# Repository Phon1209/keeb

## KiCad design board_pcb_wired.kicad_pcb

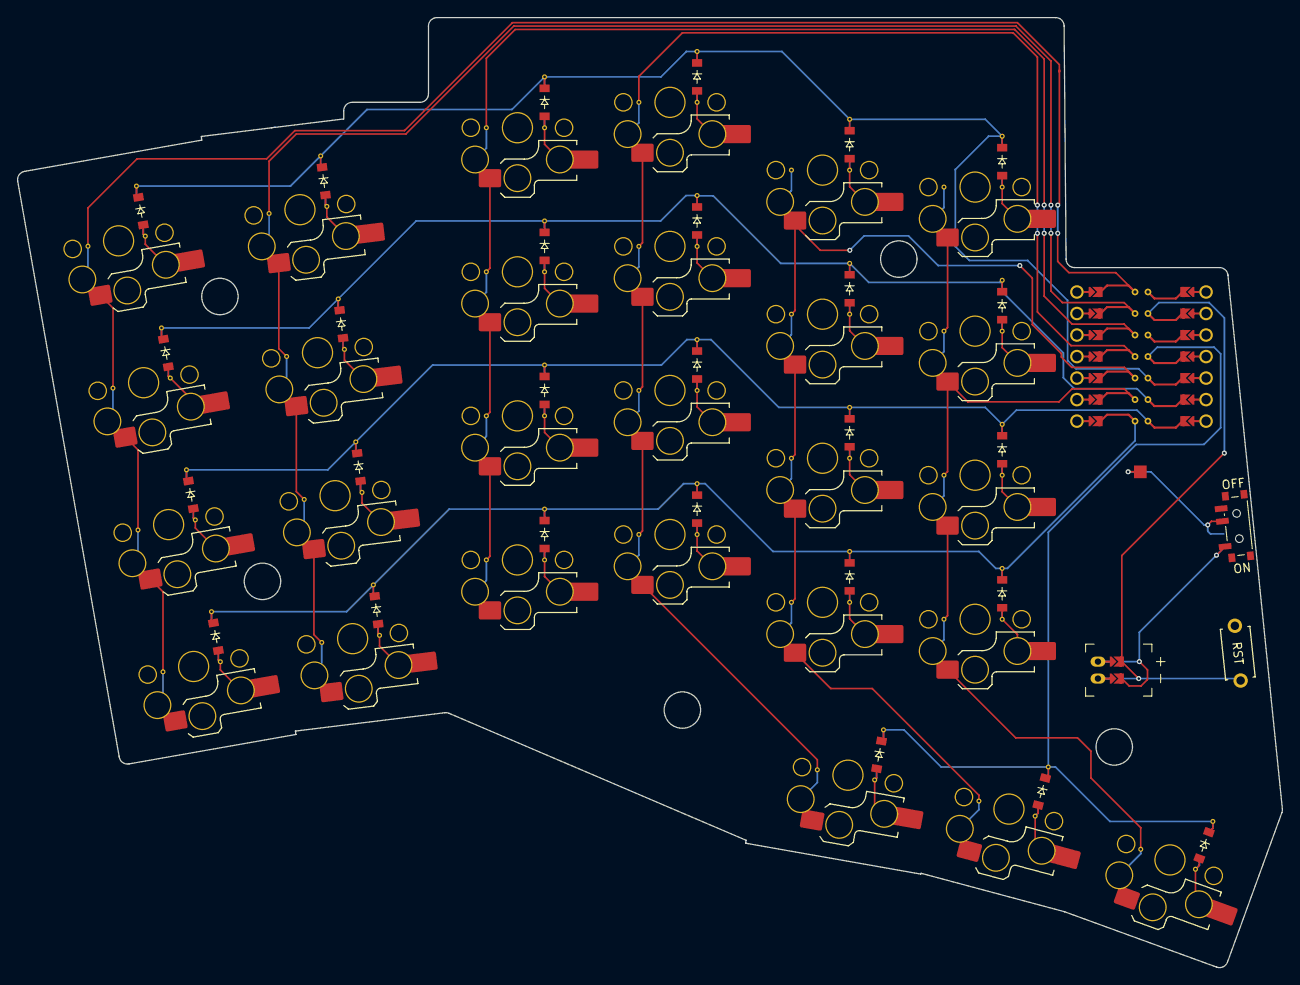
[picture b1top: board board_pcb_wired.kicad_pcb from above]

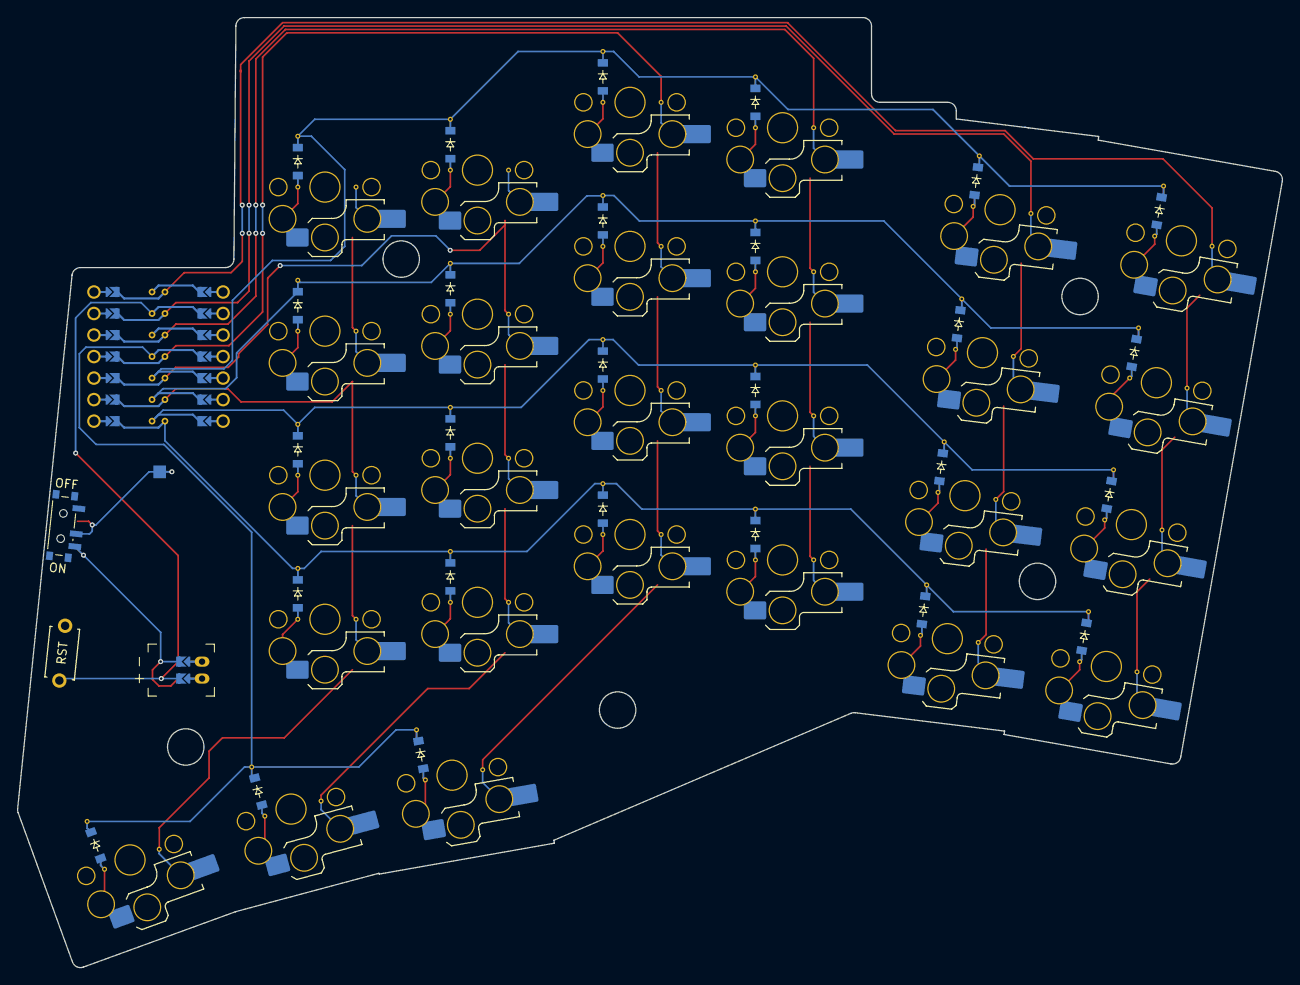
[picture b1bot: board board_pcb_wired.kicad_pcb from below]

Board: 2 copper layers, 149.3 x 112.1 mm, 59 parts (27 on the bottom side), 43 nets.

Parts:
D1, D2, D3, D4, D5, D6, D7, D8, D9, D10, D11, D12, D13, D14, D15, D16, D17, D18, D19, D20, D21, D22, D23, D24, D25, D26, D27: diode_tht_sod123
JST1: battery_connector_jst_ph_2
PAD1: SMDPad
PWR1: power_switch_smd_side
RST1: reset_switch_tht_top
S1, S2, S3, S4, S5, S6, S7, S8, S9, S10, S11, S12, S13, S14, S15, S16, S17, S18, S19, S20, S21, S22, S23, S24, S25, S26, S27: switch_choc_v1_v2
xiao-ble1: ProMicro; xiao-ble

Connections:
BAT_P: JST1.1, PWR1.1, PWR1.3
GND: JST1.2, RST1.2, xiao-ble1.2
JST1_1: JST1.11, JST1.21, JST1.31
JST1_2: JST1.12, JST1.22, JST1.32
P0: S1.2, S2.2, S3.2, S4.2, xiao-ble1.24
P1: S5.2, S6.2, S7.2, S8.2, xiao-ble1.23
P2: S9.2, S10.2, S11.2, S12.2, xiao-ble1.22
P3: S13.2, S14.2, S15.2, S16.2, S25.2, xiao-ble1.21
P4: S17.2, S18.2, S19.2, S20.2, S26.2, xiao-ble1.20
P5: S21.2, S22.2, S23.2, S24.2, S27.2, xiao-ble1.19
P6: D1.1, D5.1, D9.1, D13.1, D17.1, D21.1, xiao-ble1.18
P7: D2.1, D6.1, D10.1, D14.1, D18.1, D22.1, xiao-ble1.7
P8: D3.1, D7.1, D11.1, D15.1, D19.1, D23.1, xiao-ble1.6
P9: D4.1, D8.1, D12.1, D16.1, D20.1, D24.1, xiao-ble1.5
P10: D25.1, D26.1, D27.1, xiao-ble1.4
RAW: PAD1.1, PWR1.2
extra_pinky_bottom: D1.2, S1.1
extra_pinky_home: D2.2, S2.1
extra_pinky_top: D3.2, S3.1
extra_pinky_upper: D4.2, S4.1
far_thumb: D27.2, S27.1
home_thumb: D26.2, S26.1
index_bottom: D17.2, S17.1
index_home: D18.2, S18.1
index_top: D19.2, S19.1
index_upper: D20.2, S20.1
inner_bottom: D21.2, S21.1
inner_home: D22.2, S22.1
inner_top: D23.2, S23.1
inner_upper: D24.2, S24.1
middle_bottom: D13.2, S13.1
middle_home: D14.2, S14.1
middle_top: D15.2, S15.1
middle_upper: D16.2, S16.1
near_thumb: D25.2, S25.1
pinky_bottom: D5.2, S5.1
pinky_home: D6.2, S6.1
pinky_top: D7.2, S7.1
pinky_upper: D8.2, S8.1
ring_bottom: D9.2, S9.1
ring_home: D10.2, S10.1
ring_top: D11.2, S11.1
ring_upper: D12.2, S12.1

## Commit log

2026-04-26 Initial Ergogen design
2026-04-30 Add Kicad export from ergogen
2026-04-30 Add Seeed Xiao footprint
2026-05-01 Add connection net to the config filee
2026-05-01 Add ignore files
2026-05-01 Add ceoloide submodule
2026-05-01 Rename config file
2026-05-01 Make the board true flippable
2026-05-01 Use irreversible config for easier design
2026-05-03 Add pcb components to ergogen config
2026-05-03 Remove output directory from the repo
2026-05-03 Add triboard config as a reference
2026-05-03 Ignore output directory
2026-05-05 Update the board kicad file
2026-05-16 add arduino file for testing nRF52840
2026-05-16 Add screenshot of schematic
